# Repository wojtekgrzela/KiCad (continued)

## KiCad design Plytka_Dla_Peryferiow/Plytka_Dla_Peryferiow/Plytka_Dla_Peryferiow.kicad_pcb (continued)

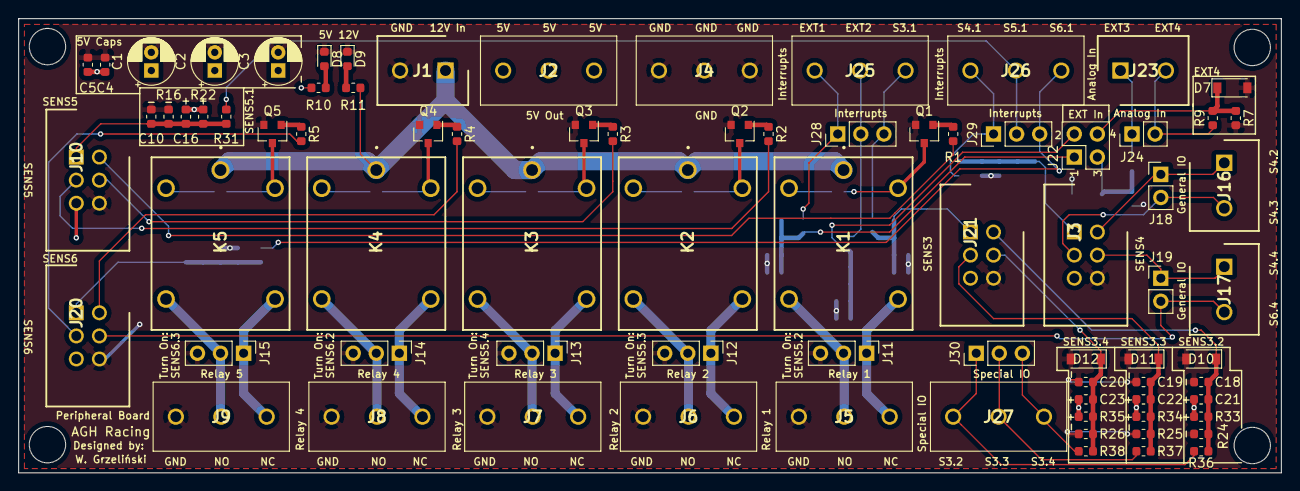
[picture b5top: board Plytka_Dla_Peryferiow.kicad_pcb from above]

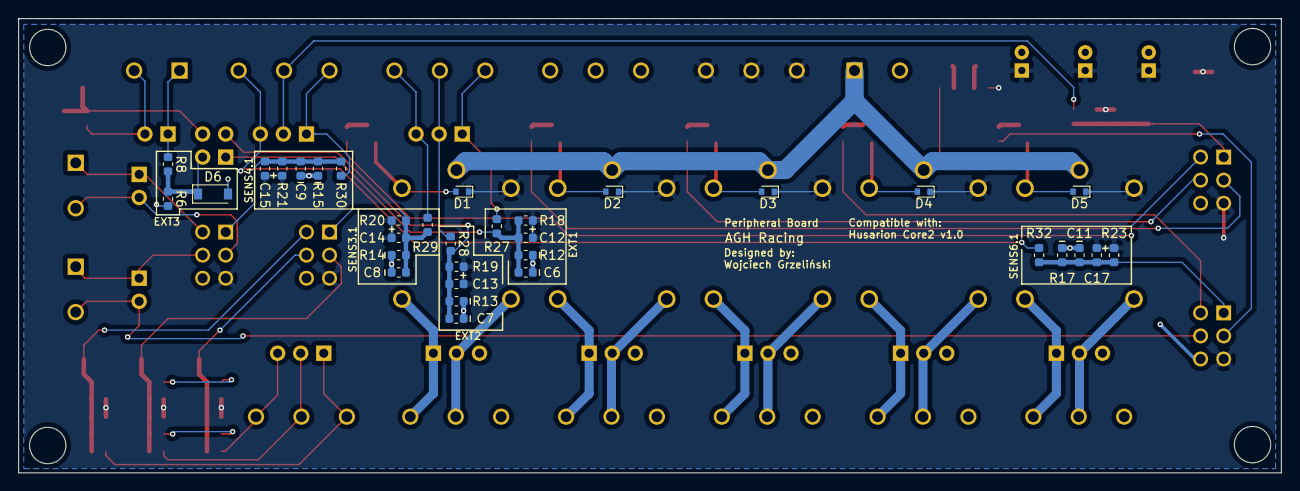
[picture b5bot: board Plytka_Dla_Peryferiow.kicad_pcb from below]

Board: 2 copper layers, 139.0 x 50.0 mm, 113 parts (33 on the bottom side), 56 nets.

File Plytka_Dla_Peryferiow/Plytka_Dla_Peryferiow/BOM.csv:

Id,Oznaczenie,Obudowa,IloÅÄ,Oznaczenie,Dostawca i numer artykuÅu,Komentarz
1,"R31,R30,R29,R28,R27",R_0603_1608Metric,5,300,https://www.tme.eu/pl/details/smd0603-300r-1%25/rezystory-sm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,
2,"R16,R15,R14,R13,R12",R_0603_1608Metric,5,10k,https://www.tme.eu/pl/details/smd0603-10k/rezystory-smd-0603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 ,
3,R11,R_0603_1608Metric,1,2k,https://www.tme.eu/pl/details/smd0603-2k-1%25/rezystory-smd-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,
4,R10,R_0603_1608Metric,1,600,https://www.tme.eu/pl/details/smd0603-620r-1%25/rezystory-sm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,"Tak, wiem, napisane jest 600 Ohmów a da³em linka do 620  jest git ;)"
5,"R5,R4,R3,R2,R1",R_0603_1608Metric,5,1k,https://www.tme.eu/pl/details/wf06p-1k-5%25/rezystory-smd-06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,
6,"Q5,Q4,Q3,Q2,Q1",SOT-23,5,Q_NPN_BEC,https://www.tme.eu/pl/details/mmbt3904-lit/tranzystory-npn-s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,
7,"K5,K4,K3,K2,K1",AZ943,5,AZ9431CH5D,https://www.tme.eu/pl/details/az943-1ch-5de/przekazniki-elek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,
8,"J30,J29,J28,J15,J14,J13,J12,J11",PinHeader_1x03_P2.54mm_Vertical,8,Conn_01x03,https://www.tme.eu/pl/details/zl201-30g/listwy-i-gniazda-kol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,"Mo¿na kupiæ kilka i bêdzie spokój, siê podzieli potem na kawa³ki"
9,"J27,J26,J25,J9,J8,J7,J6,J5,J4,J2",8719,10,ARK-3,https://www.tme.eu/pl/details/tb-5.0-p-3p/listwy-zaciskowe-d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,
10,"J24,J19,J18",PinHeader_1x02_P2.54mm_Vertical,3,Conn_01x02,https://www.tme.eu/pl/details/zl201-30g/listwy-i-gniazda-kol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,"Mo¿na kupiæ kilka i bêdzie spokój, siê podzieli potem na kawa³ki"
11,"J23,J17,J16,J1",SHDR2W99P0X500_1X2_1000X760X1000P,4,ARK-2,https://www.tme.eu/pl/details/tb-5.0-p-2p/listwy-zaciskowe-d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,
12,J22,PinHeader_2x02_P2.54mm_Vertical,1,Conn_02x02_Odd_Even,https://www.tme.eu/pl/details/zl201-30g/listwy-i-gniazda-kol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,"Mo¿na kupiæ kilka i bêdzie spokój, siê podzieli potem na kawa³ki"
13,J21,HDRV6W64P254X254_2X3_1524X895X915P,1,SENS3,https://www.tme.eu/pl/details/t821-1-06-s1/zlacza-idc/amphen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,To samo
14,J20,HDRV6W64P254X254_2X3_1524X895X915P,1,SENS6,https://www.tme.eu/pl/details/t821-1-06-s1/zlacza-idc/amphen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,
15,J10,HDRV6W64P254X254_2X3_1524X895X915P,1,SENS5,https://www.tme.eu/pl/details/t821-1-06-s1/zlacza-idc/amphen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,
16,J3,HDRV6W64P254X254_2X3_1524X895X915P,1,SENS4,https://www.tme.eu/pl/details/t821-1-06-s1/zlacza-idc/amphen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,
17,"D12,D11,D10,D7,D6",D_SOD-123,5,"3,3V",https://www.tme.eu/pl/details/bzt52c3v3-7-f/diody-zenera-smd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,
18,"D9,D8",D_0603_1608Metric,2,LED,https://www.tme.eu/pl/details/ll-s194pvc-v1-2b/diody-led-smd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 ,
19,"D5,D4,D3,D2,D1",D_SOD-523,5,D,https://www.tme.eu/pl/details/1n4148wtf-lit/diody-uniwersaln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,
20,"C10,C9,C8,C7,C6,C5,C4",C_0603_1608Metric,7,100n,https://www.tme.eu/pl/details/cc0603krx7r9104/kondensatory-m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,
21,"C3,C2,C1",CP_Radial_D5.0mm_P2.00mm,3,CP,https://www.tme.eu/pl/details/pf1v330mnn0511u/kondensatory-e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,

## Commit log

2020-03-08 Create README.md
    Added Readme
2020-03-09 Mistake in Gerber files corrected: board "table" was generated as part of the Board Outline. Therefore JLCPCB rejected the board outline file and did not want to generate drills correctly. Now everyt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
2020-03-16 First version of the schematic
2020-03-26 Update due to moving to another computer. Updated Schematic, Print-outs, PCB in development
2020-03-29 Library moved to MY_ELEMENTS
    Moved library (SamacSys) due to platform change - simplified moving between computers
2020-04-05 Added actual placement in schematic in Plytka_Dla_Peryferiow and added new elements to MY_ELEMENTS
2020-04-05 Updated schematic (DC/DC), 2-layer PCB
    Updated schematic in multiple places, added elements, exchanged 3V3 stabilizer for a DC/DC converter. Nearly finished 2-layer PCB layout.
2020-04-13 Body Computer - 4layer
    Added 4-layer board layout, changed schematic a bit, added jumper for NodeMCU powering, control MOSFET for Fans
2020-04-13 New elements
    Added new elements
2020-04-13 DRL driver - first try
    DRL driver, 2-layer board
2020-04-19 Body Computer [DONE]
    Body Computer done as a 2-layer board and put into prototype production, schematics and PCBs created.
2020-04-19 DRL Driver [DONE]
    DRL Driver done and put into production
2020-04-19 GPS Adapter [DONE]
    Gps Adapter done and put into production
2020-04-19 MOSFET Rail [DONE]
    MOSFET Rail done as a P-Channel MOSFET rail (4x) and put into production
2020-04-19 List of projects updated
2020-05-23 Gitignore update
2020-06-05 Printouts update - small changes in resistors values
2020-11-14 Initial schematic of ECU and power delivery for Jarvis V2.0
2021-02-14 Second version of the body computer - WIP
2021-02-24 Finished board design. Schematic names improvements needed.
2021-02-28 Signals naming improvements
2021-02-28 Final naming changes
2021-07-14 Schematic Update
